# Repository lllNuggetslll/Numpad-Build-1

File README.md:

# Low-profile wireless numpad

A 21-key low-profile numpad: 4 columns × 6 rows, with three 2u keys ("0", "+", "Enter").

- **Controller:** nice!nano v2, running ZMK over Bluetooth.
- **Switches:** Gateron KS-33 low-profile switches in hotswap sockets. A second PCB variant takes the
  newer **KS-33G (Low Profile 3.0)** switches instead (see [KS-33G variant](#ks-33g-variant)).
- **Battery:** a 301230 LiPo with a low-battery LED.
- **Case:** a tilted 3D-printed case with a separate switch plate.

It's based on ceoloide's "not about money" ergogen design. The PCB is generated with
[ergogen](https://ergogen.xyz), routed with freerouting, and checked in KiCad 8. The case is generated
from the board itself, so the two always match.

## Status

| Piece | State |
|---|---|
| PCB | Routed and DRC-clean. Gerbers are ready in `kicad/fab/numpad-gerbers.zip` (a PCBWay-ready package is `kicad/numpad.kicad_pcb.zip`). |
| PCB, KS-33G variant | Routed and DRC-clean: `kicad/fab_ks33g/numpad_ks33g-gerbers.zip`, PCBWay package `kicad/numpad_ks33g.kicad_pcb.zip`. |
| Case and plate | `case/case_bottom.stl`, `case/case_plate.stl` (the same case fits both boards) |
| Firmware | ZMK v0.3 shield `lp_numpad` in `config/`, built by GitHub Actions (see §4). |

Before printing the whole plate, **test-print one stabilizer cutout**. It follows Gateron's suggested mounting
drawing and was checked against the stabilizer's 3D model, but 3D-printed holes usually come out a little
small. The stabilizer should hook in at the wire end, then snap down at the other end and sit flat.

## Shopping list

See **[SHOPPING_LIST.md](SHOPPING_LIST.md)**.

## Repository layout

| Path | What it is |
|---|---|
| `config.yaml` | Ergogen source of truth for the PCB: layout, footprints, outline. |
| `footprints/ceoloide/` | Upstream ceoloide footprints. |
| `footprints/custom/` | Local footprints. `mcu_nice_nano_sparse.js` adds an `omit_pins` option; `smd_0603.js` is for the LED, resistor and capacitor; `ideal_diode_sot23_5.js` is the LTC4411 charging ideal diode; `power_switch_smd_side.js` is ceoloide's switch with a net on its OFF pin; `switch_mx_ks33g.js` is the KS-33G switch (MX sockets, Ø5.0 centre). |
| `output/` | **Current board.** `pcbs/not_about_money.kicad_pcb` is routed (DRC report `pcbs/drc.rpt`, preview `routed.svg`); `not_about_money.unrouted.kicad_pcb` is the raw ergogen output. |
| `kicad/` | KiCad project for the current board (with the project's 0.2 mm edge-clearance rule), `fab/` (gerbers + drill + zip), and the PCBWay package `numpad.kicad_pcb.zip`. The KS-33G variant is a second project in the same folder: `numpad_ks33g.kicad_pro`, `fab_ks33g/`, `numpad_ks33g.kicad_pcb.zip`. |
| `case/build_case.py` | Generates the case from the board: `case_bottom.jscad`, `case_plate.jscad`, `assembly.json`. |
| `case/viewer.html` | 3D viewer of the case, plate, PCB, parts, keycaps and battery. |
| `case/battery_fit.py` | Finds where LiPo cells fit under the tilted PCB. |
| Git history | Earlier design iterations (commit `c19e498` has every old `output_*` folder and config backup). |
| `CLAUDE.md` | Detailed design notes: coordinates, measurements, decisions, gotchas. |

## KS-33G variant

Gateron's **KS-33G** switches (Low Profile 3.0, e.g. Silent Red KS-33GJH10B045NW-X5B) look like the KS-33 from
the top: same 14.00 mm plate cutout, same 2.50 mm from the PCB to the plate top, same plate. Underneath they're
different. They use the **MX pin layout** (Ø1.5 pins), two Ø1.7 plastic pegs, and a **Ø5.0 centre post**, so
they need MX-style hotswap sockets and a different PCB. Only the switch footprints differ; everything else is the
same board.

| | KS-33 board (`numpad.kicad_pcb`) | KS-33G board (`numpad_ks33g.kicad_pcb`) |
|---|---|---|
| Switch | Gateron KS-33 (Low Profile 2.0) | Gateron KS-33G (Low Profile 3.0) |
| Hotswap socket | Gateron LP 2.0, KS-2P02B01-**02** | MX-pattern socket: Gateron KS-2P02B01-**01** or Kailh CPG151101S11 |
| Socket sanding on the 2u keys | yes (step 1 below) | no |
| Case, plate, stabilizers, nice!nano, firmware pin map | same | same |

- The two sockets under the nice!nano (the top two keys of column 2) are turned a different way from the
  others so they clear its pins. The diodes next to them sit 0.8 mm further right.
- **Test-fit one 2u key before buying a full set of switches.** Put a KS-33G, a KS-57 stabilizer and a 2u
  keycap together and press each end of the key. Both ends should bottom out as firmly as the middle. The
  stabilizers line up exactly as on the KS-33 board, but the KS-33G travels 3.2 mm (±0.2), and the stabilizer's
  actuator only has about 3.25 mm before it hits its housing. A long-travel switch could leave the ends of a 2u
  key stopping ~0.15 mm short.
- **Measure the MX sockets before you order the board.** The socket body height is an estimate (1.85 mm). It
  has to stay under ~2.3 mm, because two of the sockets sit under the nice!nano, whose USB-C shell starts
  2.3 mm below the PCB on its stock headers.
- The KS-33G's centre post reaches 3.70 mm below its seat (0.45 mm more than the KS-33). The case check
  still finds no collisions, and the battery spot and screw lengths don't change.

## 1. Order the PCB

Upload `kicad/fab/numpad-gerbers.zip` to any PCB fab (for KS-33G switches: `kicad/fab_ks33g/numpad_ks33g-gerbers.zip`
and `kicad/numpad_ks33g.kicad_pcb.zip`). For PCBWay, `kicad/numpad.kicad_pcb.zip` already includes their BOM, netlist and positions files. Order a 2-layer, 1.6 mm, standard-spec board. The
design values (0.25 mm tracks, 0.2 mm clearance, 0.6/0.3 mm vias) are within every fab's limits. The three
stabilizer cutouts are part of the board outline.

## 2. Print the case

- **`case/case_bottom.stl`:** print as-is (floor down). It has a 0.5 mm battery pocket in the floor and three
  windows in the back wall: USB-C, reset, and the power-switch lever. The USB-C port sits at the back of a
  12.5 × 6.5 mm recess so a cable head can reach it; the recess's back wall is flush with the port.
- **`case/case_plate.stl`:** print **upside down** (plate top on the bed). The edge rim and the spacer posts
  around the screws are on its underside.
- **Settings:** PLA or PETG, 0.2 mm layers. No supports needed.

## 3. Assemble

The switches go on the front of the PCB. **Everything else** goes on the back (side B), except the
low-battery LED, which is on the front.

1. **Trim three sockets** (KS-33 board only; skip this on the KS-33G board). On the hotswap sockets for the three 2u keys ("0", "+", "Enter"), sand
   **1.1 mm off the tip of the solder tab that points at the stabilizer cutout**, leaving about 1.4–1.5 mm of
   tab. Without this, that tab hits the stabilizer housing. Dry-fit each socket to find the right tab, then
   clean and tin it.
2. **Back side SMD parts:** solder the 21 diodes (mind the cathode band), the 21 hotswap sockets, the reset
   button, the power switch, the 1 kΩ resistor, and the charging parts right of the power switch: **IC1**
   (LTC4411, SOT-23-5; pin 1 is the corner marked on the silkscreen, by the switch) and **C1** (1 µF 0603).
   These let USB charge the battery with the power switch **off** (see *Charging* below).
3. **Front side:** solder the 0603 LED. It sits under a hole in the plate between the keycaps.
4. **Battery connector:** solder the JST PH on the back, then **trim its pins flush** on the front. They're
   3.4 mm long and poke 1.8 mm through; the plate only leaves 1.9 mm above the PCB.
   - **Boards made from files before 2026-11-07** (the JST's two holes sit 3 mm closer to the top edge than
     on the current board): the connector's body lands on the socket of the key to its right, so it can't be
     fitted. Leave it off and
     solder the battery leads straight into its two holes (+ into the oval pad 2, − into pad 1).
5. **nice!nano:** the controller mounts on the back, components facing **away** from the PCB, on standard
   the male header pins that come with it. They seat it 2.3 mm off the PCB (measured), which is what the
   case's USB-C window is built for; other headers must seat it within ±0.2 mm of that.
   - Fit pins **only** where the PCB has holes: 16 pins (RAW, RST, GND ×2, P0, P1, P4–P8, P14–P16, P18,
     P19). The other 8 positions sit over switch pads and are left off on purpose.
   - Trim the pins on the front to about 1.4 mm, **except** the 7 pins in the row nearer the board's left
     edge: RAW, GND, RST at the USB end, and P18, P15, P14, P16 at the far end. Those 7 come up
     *under* the two switches above the nano (2nd column, top two rows). The switch bottom sits flat on the
     PCB there. Cut them **flush** and file the solder flat (≤ ~0.2 mm), or the switches won't seat. If you
     socket the nano, the socket tails there need the same treatment.
6. **Battery:**
   - **Check polarity first.** On the JST footprint, the oval pad (pad 2) is **battery +** and the
     squarer pad (pad 1) is **battery −**. Many cheap LiPos have their plug wired the other way round.
     Measure with a multimeter before plugging in.
   - Stick the 301230 into the floor pocket with thin double-sided tape. Its lead runs from the notch at the
     pocket's end to the JST.
7. **Plate, stabilizers and switches:**
   - Clip the stabilizers into the plate. The wire bar faces the middle of the board.
   - Press the switches into the plate.
   - Lower the plate onto the PCB so the switch pins enter the sockets.
8. **Into the case:** angle the PCB in at the back first and slide it back, so the power lever slips
   through its window (it pokes about 0.5 mm out of the back) and the USB-C port slides into its window
   (it sits inside the wall, so it can't drop in from above). Then drop
   the front onto the pillars.
9. **Screws:** fit the countersunk M2 screws through the plate. Use **M2×8** at the back-left, back-right and
   centre pillars, and **M2×6** at the two front pillars. Tighten gently; they cut their own thread in the
   plastic.
10. **Keycaps.**

## 4. Firmware (ZMK)

The ZMK config is in `config/` (shield `lp_numpad`, pinned to ZMK v0.3, board `nice_nano_v2`):
`boards/shields/lp_numpad/lp_numpad.overlay` (matrix pins), `lp_numpad.keymap`, `lp_numpad.conf`, `build.yaml`.
GitHub Actions (`.github/workflows/build.yml`) builds it on every push that touches `config/`.

The matrix is 4 columns × 6 rows, diodes column → row (`col2row`):

| Signal | nice!nano pin |
|---|---|
| Columns C1–C4 | P19, P18, P15, P14 |
| Row R1 | P16 |
| Rows R2–R6 | P4, P5, P6, P7, P8 |
| Low-battery LED (active high) | P0 (nRF P0.08) |
| Free spare | P1 |

**Flashing:**
1. Push, open the repo's **Actions** tab, open the latest "Build ZMK firmware" run and download the
   `firmware` artifact. It holds `lp_numpad-nice_nano_v2-zmk.uf2` and `settings_reset-nice_nano_v2-zmk.uf2`.
2. Plug the numpad into USB and **double-press the reset button** (paperclip through the rear wall). A drive
   called `NICENANO` appears.
3. First flash only: copy `settings_reset-…uf2` onto it. The drive vanishes and reboots. Double-press reset again.
4. Copy `lp_numpad-…uf2` onto it. The drive vanishes when it's done. Windows may say the copy failed; that's normal.
5. Pair: Windows Settings → Bluetooth & devices → Add device → Bluetooth → **LP Numpad** (with USB unplugged,
   the power switch must be on).

**Charging:** USB charges the battery through the nice!nano's charger (about 100 mA, so roughly 1–1.5 h for a
301230 cell; it stops by itself when full).
- Switch **on**: the battery is wired straight to the nano and charges to 100 %.
- Switch **off** (boards from 2026-11-23 on): in the off position the switch connects the nano to IC1, an
  LTC4411 ideal diode, which charges the battery through a regulated ~28 mV drop (to about 4.17 V, ~97 %) and
  blocks the battery from the nano once USB is unplugged, so off still means off.
- **Older boards (no IC1/C1 pads):** charging only works with the switch on. Optional bodge: a SOD-123 Schottky
  (e.g. B5819W) from the switch's free pin (pad 3, anode) to its battery pin (pad 1, cathode/band). That charges
  with the switch off too, but only to about 4.0 V (~85 %) because of the diode drop.

**Keymap:** the top row is Esc, Tab, Backspace, Fn; below it a standard numpad. Hold **Fn** (top right) for:
Esc = bootloader (re-flash without the paperclip), Tab = reboot, NumLock = clear the current Bluetooth
pairing, `-` = toggle USB/BLE, 7/8/9 = Bluetooth profile 1/2/3, 1/2 = previous/next profile, 4/5/6 =
previous/play/next track, 3 = mute, `+`/Enter = volume up/down, 0/. = output USB/BLE.
The keypad keys need NumLock on; on Windows, numpad keys act as arrows when it's off.

VCC (3.3 V out) isn't connected. ZMK has no built-in low-battery LED, so blinking P0 when the battery is low
needs a small custom module (not written yet). Keep it to a blink, because a steady LED drains the battery.

## Rebuilding from source

Requires ergogen v4.1.0 (`npm i -g ergogen@4.1.0`), KiCad 8 (its bundled Python provides `pcbnew`), and Java
15+ for freerouting 1.4.5.1.

1. **Generate the PCB.** Custom footprints only load when ergogen gets a *directory*. Copy `config.yaml` and
   `footprints/` into a scratch folder, then run:
   ```bash
   ergogen <scratch-folder> -o <scratch-folder>/out --clean
   ```
   This builds both boards: `not_about_money` (KS-33) and `numpad_ks33g` (KS-33G). Both come out
   unrouted. Save them as `output/pcbs/*.unrouted.kicad_pcb`, and copy `out/outlines` and `out/cases` over the
   ones in `output/`. Don't point ergogen
   at `output/` directly: `--clean` empties the whole folder, including the routed board.
2. **Route it.** Export a Specctra DSN with `pcbnew.ExportSpecctraDSN`, then route:
   ```bash
   java -jar freerouting-1.4.5.1.jar -de board.dsn -do board.ses -mp 30
   ```
   Import the result with `pcbnew.ImportSpecctraSES`. Set copper-to-edge clearance to 0.2 mm (the side
   switches sit at the board edge), then run DRC:
   ```bash
   kicad-cli pcb drc --severity-error board.kicad_pcb
   ```
3. **Gerbers:**
   ```bash
   kicad-cli pcb export gerbers --output fab/ board.kicad_pcb
   ```
   ```bash
   kicad-cli pcb export drill --output fab/ board.kicad_pcb
   ```
   Then zip the `fab/` folder.
4. **Case.** Point `BOARD` at the top of `case/build_case.py` to the board, then run it with KiCad's Python. It
   prints the stack-up, a collision report, the battery spot and the screw lengths.
   ```bash
   "C:/Program Files/KiCad/8.0/bin/python.exe" case/build_case.py
   ```
   Render the jscad files to STL with the **v1** JSCAD CLI (v2 can't run them):
   ```bash
   npm install --prefix .jscad @jscad/cli@1
   ```
   ```bash
   .jscad/node_modules/.bin/openjscad case/case_bottom.jscad -o case/case_bottom.stl
   ```
   ```bash
   .jscad/node_modules/.bin/openjscad case/case_plate.jscad -o case/case_plate.stl
   ```
5. **View it.** Serve the case folder and open `http://localhost:8765/viewer.html`:
   ```bash
   python -m http.server 8765 --directory case
   ```

`CLAUDE.md` has the full design notes: the tilt and stack-up, where each part dimension came from (datasheet
vs estimate), the stabilizer geometry, and the controller pin constraints.

## Credits and licenses

- The base design and most footprints are by [ceoloide](https://github.com/ceoloide), with contributions by
  @infused-kim and @nxtk; see `footprints/ceoloide/LICENSE`.
- Some footprints are **CC BY-NC-SA 4.0**: the nice!nano and power-switch footprints, and therefore
  `footprints/custom/mcu_nice_nano_sparse.js`, which is derived from one of them. Others are MIT. Check the
  header of each file.
- The non-commercial clause means boards built from this repo shouldn't be sold.

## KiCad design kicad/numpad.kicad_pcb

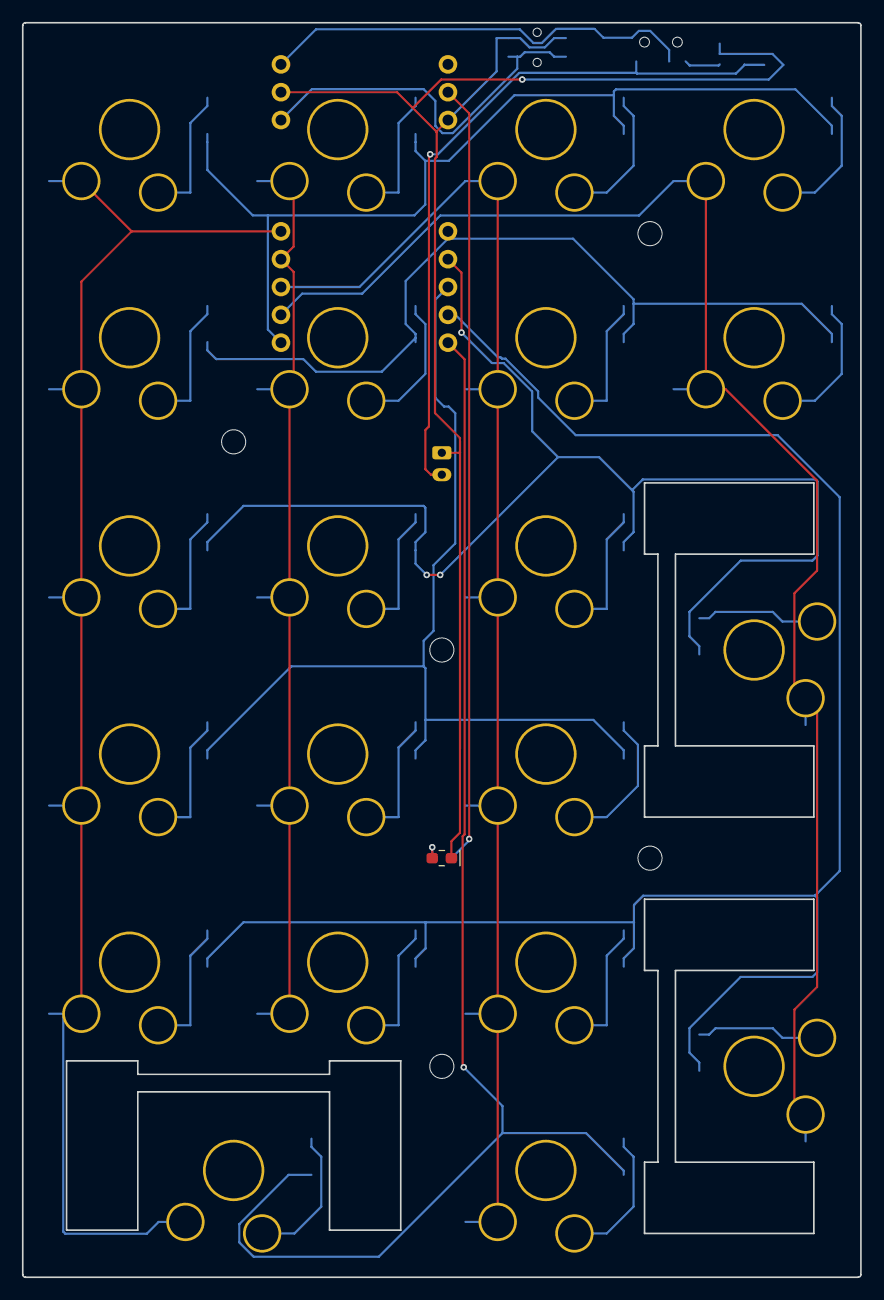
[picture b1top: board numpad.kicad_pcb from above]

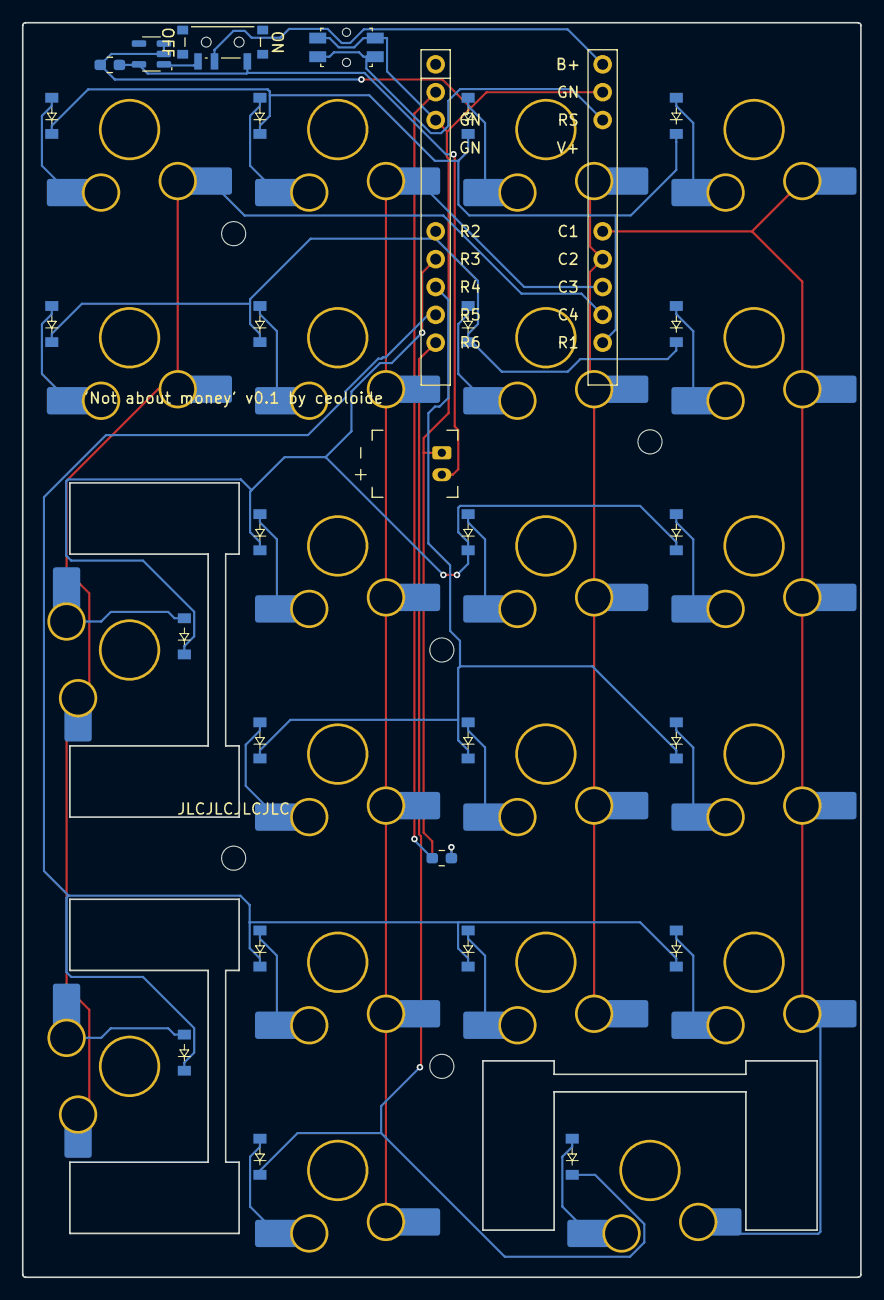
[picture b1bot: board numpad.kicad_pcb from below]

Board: 2 copper layers, 76.5 x 114.5 mm, 55 parts (49 on the bottom side), 38 nets.

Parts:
C1: 1uF X5R 10V; smd_0603
D1, D2, D3, D4, D5, D6, D7, D8, D9, D10, D11, D12, D13, D14, D15, D16, D17, D18, D19, D20, D21: diode_tht_sod123
IC1: LTC4411; ideal_diode_sot23_5
JST1: battery_connector_jst_ph_2
LED1: LTST-C191KRKT; smd_0603
MCU1: mcu_nice_nano
MH1, MH2, MH3, MH4, MH5: mounting_hole_npth
PWR1: power_switch_smd_side
R1: 1k; smd_0603
RST1: reset_switch_smd_side
S1, S2, S3, S4, S5, S6, S7, S8, S9, S10, S11, S12, S13, S14, S15, S16, S17, S18, S19, S20, S21: switch_gateron_ks27_ks33

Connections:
BAT_P: C1.2, IC1.5, JST1.2, PWR1.1
C1: MCU1.18, S1.1, S2.1, S3.1, S4.1, S5.1, S19.1
C2: MCU1.17, S6.1, S7.1, S8.1, S9.1, S10.1
C3: MCU1.16, S11.1, S12.1, S13.1, S14.1, S15.1, S16.1
C4: MCU1.15, S17.1, S18.1, S20.1, S21.1
CHG_IN: IC1.1, PWR1.3
GND: C1.1, IC1.2, IC1.3, JST1.1, LED1.2, MCU1.3, MCU1.23, RST1.1, RST1.3
LED_A: LED1.1, R1.2
P0: MCU1.2, R1.1
R1: D6.1, D11.1, D17.1, D19.1, MCU1.14
R2: D5.1, D10.1, D16.1, D18.1, MCU1.7
R3: D4.1, D9.1, D15.1, D21.1, MCU1.8
R4: D3.1, D8.1, D14.1, MCU1.9
R5: D2.1, D7.1, D13.1, D20.1, MCU1.10
R6: D1.1, D12.1, MCU1.11
RAW: MCU1.24, PWR1.2
RST: MCU1.22, RST1.2, RST1.4
c1_r1: D6.2, S5.2
c1_r2: D5.2, S4.2
c1_r3: D4.2, S3.2
c1_r4: D3.2, S2.2
c1_r5: D2.2, S1.2
c1_r6: D1.2, S19.2
c2_r1: D11.2, S10.2
c2_r2: D10.2, S9.2
c2_r3: D9.2, S8.2
c2_r4: D8.2, S7.2
c2_r5: D7.2, S6.2
c3_r1: D17.2, S16.2
c3_r2: D16.2, S15.2
c3_r3: D15.2, S14.2
c3_r4: D14.2, S13.2
c3_r5: D13.2, S12.2
c3_r6: D12.2, S11.2
c4_r1: D19.2, S18.2
c4_r2: D18.2, S17.2
c4_r3: D21.2, S21.2
c4_r5: D20.2, S20.2
